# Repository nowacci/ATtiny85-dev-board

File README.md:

# ATtiny85-dev-board
A development board for the ATtiny85 to program the MCU directly through the Arduino UNO using an AVR USB programmer, which has a 10-pin reset button input along with output pins.

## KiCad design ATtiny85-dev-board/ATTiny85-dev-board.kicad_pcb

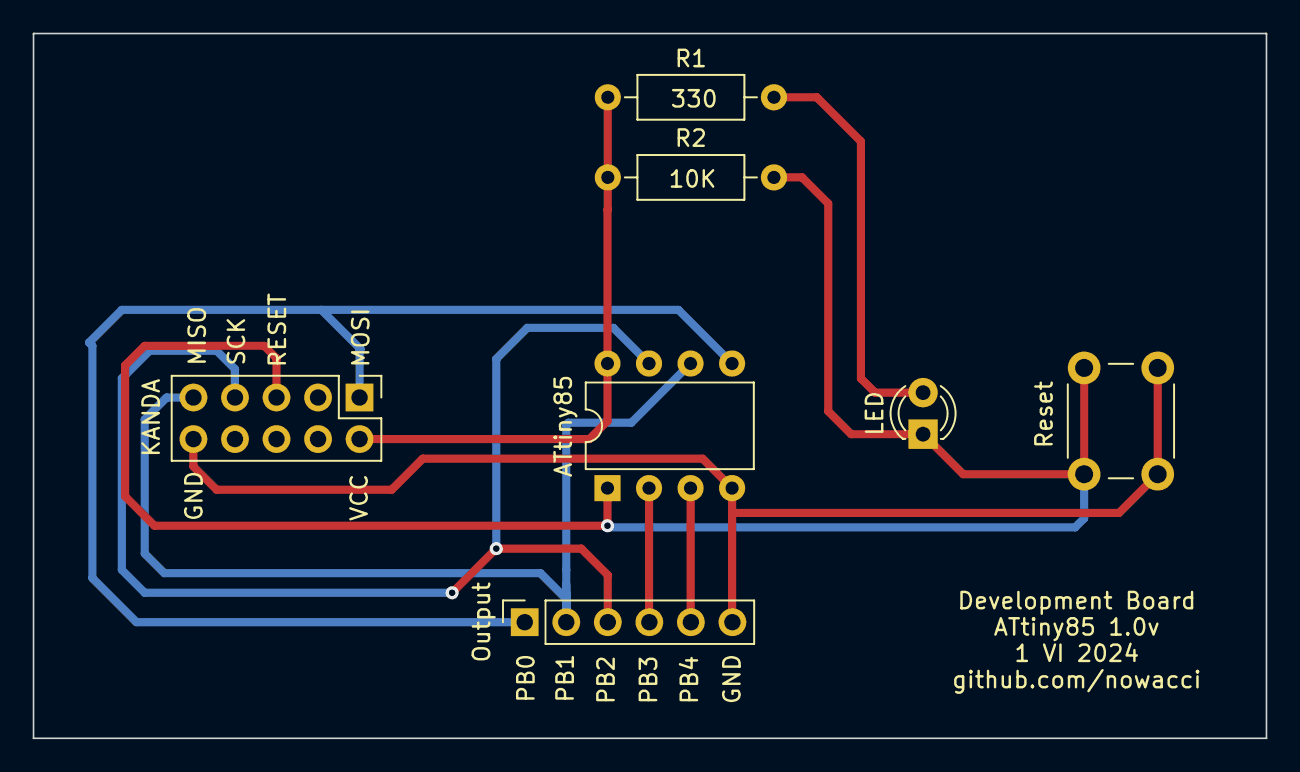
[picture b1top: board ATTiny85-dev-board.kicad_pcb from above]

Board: 2 copper layers, 75.4 x 43.1 mm, 7 parts (0 on the bottom side), 9 nets.

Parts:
J1: KANDA; PinHeader_2x05_P2.54mm_Vertical
J2: Output; PinSocket_1x06_P2.54mm_Vertical
LED: LED; LED_D3.0mm
R1: 330; R_Axial_DIN0207_L6.3mm_D2.5mm_P10.16mm_Horizontal
R2: 10K; R_Axial_DIN0207_L6.3mm_D2.5mm_P10.16mm_Horizontal
Reset: RESET; SW_PUSH_6mm_H4.3mm
U1: ATtiny85; DIP-8_W7.62mm

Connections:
unnamed: LED.2 (A), R1.2
unnamed: J1.5, LED.1 (K), R2.2, Reset.2, U1.1 (~RESET/PB5)
unnamed: J1.1, J2.1, U1.5 (AREF/PB0)
unnamed: J1.2, R1.1, R2.1, U1.8 (VCC)
unnamed: J1.7, J2.3, U1.7 (PB2)
unnamed: J1.9, J2.2, U1.6 (PB1)
unnamed: J1.10, J2.6, Reset.1, U1.4 (GND)
unnamed: J2.4, U1.2 (XTAL1/PB3)
unnamed: J2.5, U1.3 (XTAL2/PB4)

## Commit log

2024-06-01 Version 1.0v
